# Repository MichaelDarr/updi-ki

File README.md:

# updi-ki

This project was forked from [Updi-Key](https://github.com/Dlloydev/Updi-Key).

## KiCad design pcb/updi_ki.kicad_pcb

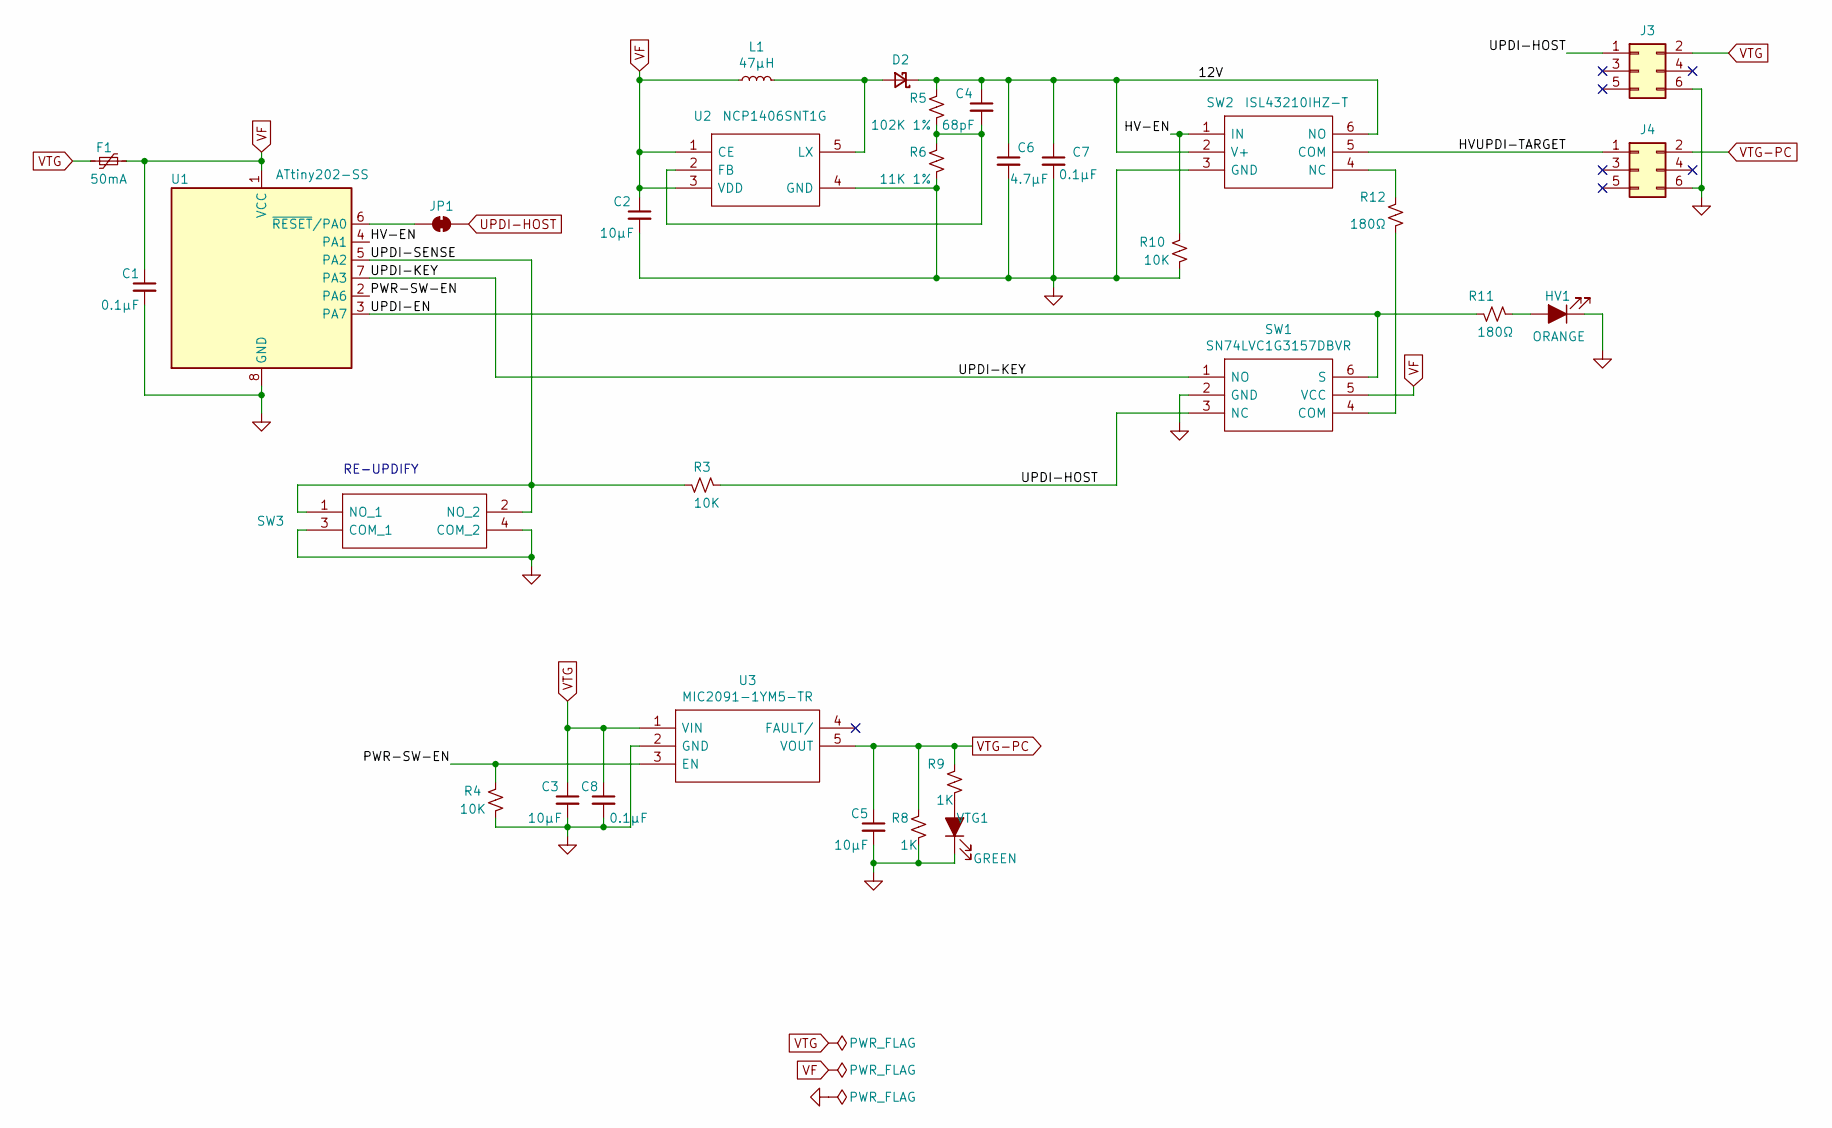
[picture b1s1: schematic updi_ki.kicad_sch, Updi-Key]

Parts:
C1, C7, C8: 0.1µF; C_0603_1608Metric; Manufacturer_Part_Number CL10B104KB8NNNC; Digi-Key Part Number 1276-1000-1-ND
C2, C3, C5: 10µF; C_0603_1608Metric; Manufacturer_Part_Number LMK107BBJ106MALT; Digi-Key Part Number 587-3258-1-ND
C4: 68pF; C_0603_1608Metric; Manufacturer_Part_Number CC0603BRNPO9BNR68; Digi-Key Part Number 311-3842-1-ND
C6: 4.7µF; C_0603_1608Metric; Manufacturer_Part_Number CL10A475KO8NNNC; Digi-Key Part Number 1276-1784-1-ND
D2: PMEG4005CEJX; D_SOD-323F; Manufacturer_Part_Number PMEG4005CEJX; Digi-Key Part Number 1727-8169-1-ND
F1: 50mA; Fuse_0603_1608Metric; Manufacturer_Part_Number 0ZCM0005FF2G; Digi-Key Part Number 507-1816-1-ND
HV1: ORANGE; LED_0603_1608Metric; Manufacturer_Part_Number APTD1608SECK/J4-PF; Digi-Key Part Number 754-1802-1-ND
J3: UPDI_IN6; PinHeader_2x03_P2.54mm_Vertical
J4: HVUPDI_OUT6; PinHeader_2x03_P2.54mm_Vertical
JP1: SolderJumper_2_Bridged; SolderJumper-2_P1.3mm_Bridged_RoundedPad1.0x1.5mm
L1: 47µH; L_1008_2520Metric; Manufacturer_Part_Number CBC2518T470K; Digi-Key Part Number 587-3060-1-ND
R3, R4, R10: 10K; R_0603_1608Metric; Manufacturer_Part_Number RK73B1JTTD103J; Digi-Key Part Number 2019-RK73B1JTTD103JCT-ND
R5: 102K 1%; R_0603_1608Metric; Manufacturer_Part_Number RC0603FR-07102KL; Digi-Key Part Number 311-102KHRCT-ND
R6: 11K 1%; R_0603_1608Metric; Manufacturer_Part_Number RC0603FR-0711KL; Digi-Key Part Number 311-11.0KHRCT-ND
R8, R9: 1K; R_0603_1608Metric; Manufacturer_Part_Number RK73B1JTTD102J; Digi-Key Part Number 2019-RK73B1JTTD102JCT-ND
R11, R12: 180Ω; R_0603_1608Metric; Manufacturer_Part_Number RK73B1JTTD181J; Digi-Key Part Number 2019-RK73B1JTTD181JCT-ND
SW1: SN74LVC1G3157DBVR; SOT95P280X145-6N; Manufacturer_Part_Number SN74LVC1G3157DBVR; Mouser Part Number 595-SN74LVC1G3157DBV
SW2: ISL43210IHZ-T; SOT95P280X145-6N; Manufacturer_Part_Number ISL43210IHZ-T; Mouser Part Number 968-ISL43210IHZ-T
SW3: PTS810SJG250SMTRLFS; Manufacturer_Part_Number PTS810SJG250SMTRLFS; Mouser Part Number 611-PTS810SJG250SMTR
U1: ATtiny202-SS; SOIC-8_3.9x4.9mm_P1.27mm; Manufacturer_Part_Number ATTINY202-SSNR; Digi-Key Part Number ATTINY202-SSNRCT-ND
U2: NCP1406SNT1G; SOT95P275X110-5N; Manufacturer_Part_Number NCP1406SNT1G; Mouser Part Number 863-NCP1406SNT1G
U3: MIC2091-1YM5-TR; SOT95P280X130-5N; Manufacturer_Part_Number MIC2091-1YM5-TR; Mouser Part Number 998-MIC2091-1YM5TR
VTG1: GREEN; LED_0603_1608Metric; Manufacturer_Part_Number LG Q396-PS-35; Digi-Key Part Number 475-3754-1-ND

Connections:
/12V: C4.1, C6.1, C7.1, D2.1 (K), R5.1, SW2.2 (V+), SW2.6 (NO)
/HV-EN: R10.1, SW2.1 (IN), U1.4 (PA1)
/HVUPDI-TARGET: J4.1, SW2.5 (COM)
/PWR-SW-EN: R4.1, U1.2 (PA6), U3.3 (EN)
/UPDI-EN: R11.2, SW1.6 (S), U1.3 (PA7)
/UPDI-KEY: SW1.1 (NO), U1.7 (PA3)
/UPDI-SENSE: R3.1, SW3.1 (NO_1), SW3.2 (NO_2), U1.5 (PA2)
GND: C1.2, C2.2, C3.2, C5.2, C6.2, C7.2, C8.2, HV1.1 (K), J3.6, J4.6, R4.2, R6.2, R8.2, R10.2, SW1.2 (GND), SW2.3 (GND), SW3.3 (COM_1), SW3.4 (COM_2), U1.8 (GND), U2.4 (GND), U3.2 (GND), VTG1.1 (K)
unnamed: D2.2 (A), L1.2, U2.5 (LX)
unnamed: HV1.2 (A), R11.1
unnamed: JP1.1 (A), U1.6 (~RESET/PA0)
unnamed: R12.2, SW1.4 (COM)
unnamed: R12.1, SW2.4 (NC)
unnamed: C4.2, R5.2, R6.1, U2.2 (FB)
unnamed: R9.2, VTG1.2 (A)
UPDI-HOST: J3.1, JP1.2 (B), R3.2, SW1.3 (NC)
VF: C1.1, C2.1, F1.1, L1.1, SW1.5 (VCC), U1.1 (VCC), U2.1 (CE), U2.3 (VDD)
VTG: C3.1, C8.1, F1.2, J3.2, U3.1 (VIN)
VTG-PC: C5.1, J4.2, R8.1, R9.1, U3.5 (VOUT)

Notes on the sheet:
RE-UPDIFY

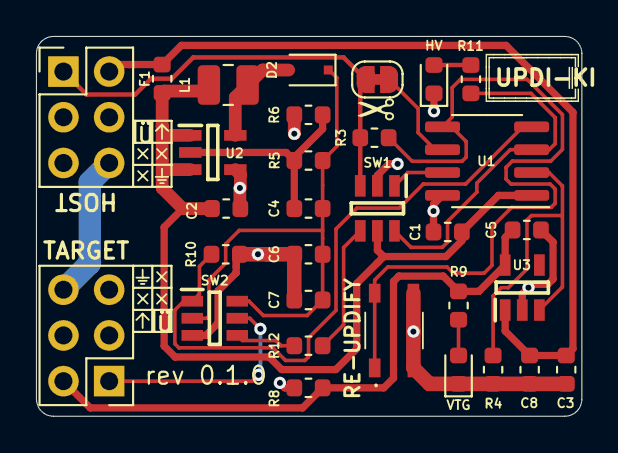
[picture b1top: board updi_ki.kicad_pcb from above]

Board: 2 copper layers, 30.3 x 21.1 mm, 31 parts (0 on the bottom side), 19 nets.

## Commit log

2024-01-07 updi-ki
2024-01-07 Condense layout
2024-01-07 Remove unhelpful layers
